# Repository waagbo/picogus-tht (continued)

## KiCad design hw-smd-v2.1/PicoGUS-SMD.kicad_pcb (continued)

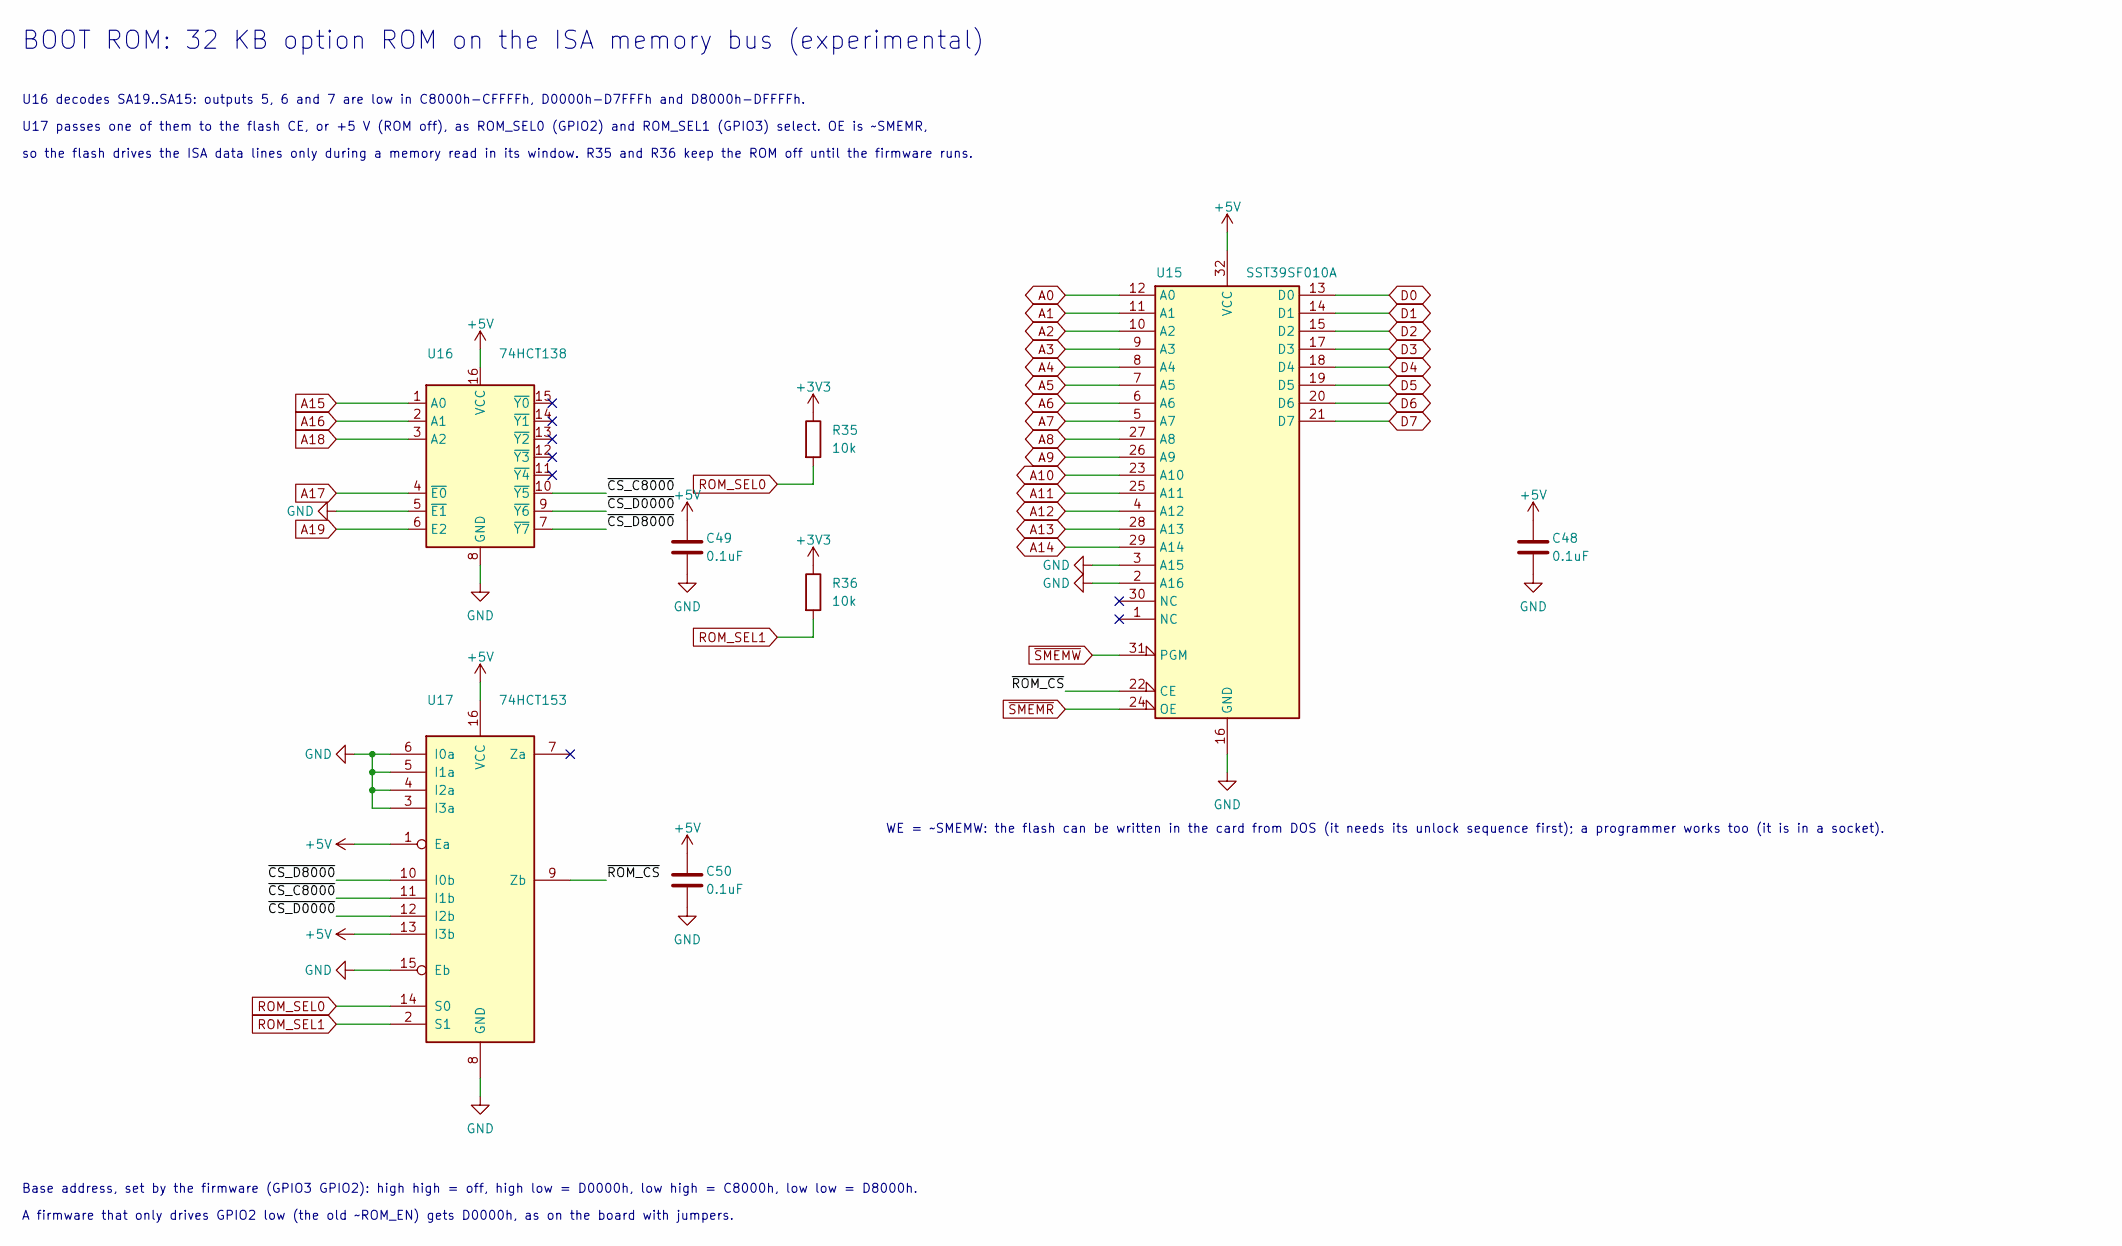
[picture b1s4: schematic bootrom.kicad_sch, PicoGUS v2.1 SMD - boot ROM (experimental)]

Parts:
C48, C49, C50: 0.1uF; C_0805_2012Metric_Pad1.18x1.45mm_HandSolder; MPN CL21B104KBCNNNC; DigiKey 1276-1003-1-ND
R35, R36: 10k; R_0805_2012Metric_Pad1.20x1.40mm_HandSolder; MPN RC0805FR-0710KL; DigiKey 311-10.0KCRCT-ND
U15: SST39SF010A; PLCC-32_THT-Socket; MPN SST39SF010A-70-4C-NHE; DigiKey SST39SF010A-70-4C-NHE-ND
U16: 74HCT138; SOIC-16_3.9x9.9mm_P1.27mm; MPN 74HCT138D,653; DigiKey 1727-2835-1-ND
U17: 74HCT153; SOIC-16_3.9x9.9mm_P1.27mm; MPN 74HCT153D,653; DigiKey 1727-74HCT153D,653CT-ND

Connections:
+3V3: R35.1, R36.1; also elsewhere on the board
+5V: C48.1, C49.1, C50.1, U15.32 (VCC), U16.16 (VCC), U17.1 (Ea), U17.13 (I3b), U17.16 (VCC); also elsewhere on the board
/Boot ROM/~CS_C8000: U16.10 (~Y5), U17.11 (I1b)
/Boot ROM/~CS_D0000: U16.9 (~Y6), U17.12 (I2b)
/Boot ROM/~CS_D8000: U16.7 (~Y7), U17.10 (I0b)
/Boot ROM/~ROM_CS: U15.22 (CE), U17.9 (Zb)
A0: U15.12 (A0); also elsewhere on the board
A1: U15.11 (A1); also elsewhere on the board
A2: U15.10 (A2); also elsewhere on the board
A3: U15.9 (A3); also elsewhere on the board
A4: U15.8 (A4); also elsewhere on the board
A5: U15.7 (A5); also elsewhere on the board
A6: U15.6 (A6); also elsewhere on the board
A7: U15.5 (A7); also elsewhere on the board
A8: U15.27 (A8); also elsewhere on the board
A9: U15.26 (A9); also elsewhere on the board
A10: U15.23 (A10); also elsewhere on the board
A11: U15.25 (A11); also elsewhere on the board
A12: U15.4 (A12); also elsewhere on the board
A13: U15.28 (A13); also elsewhere on the board
A14: U15.29 (A14); also elsewhere on the board
A15: U16.1 (A0); also elsewhere on the board
A16: U16.2 (A1); also elsewhere on the board
A17: U16.4 (~E0); also elsewhere on the board
A18: U16.3 (A2); also elsewhere on the board
A19: U16.6 (E2); also elsewhere on the board
D0: U15.13 (D0); also elsewhere on the board
D1: U15.14 (D1); also elsewhere on the board
D2: U15.15 (D2); also elsewhere on the board
D3: U15.17 (D3); also elsewhere on the board
D4: U15.18 (D4); also elsewhere on the board
D5: U15.19 (D5); also elsewhere on the board
D6: U15.20 (D6); also elsewhere on the board
D7: U15.21 (D7); also elsewhere on the board
GND: C48.2, C49.2, C50.2, U15.2 (A16), U15.3 (A15), U15.16 (GND), U16.5 (~E1), U16.8 (GND), U17.3 (I3a), U17.4 (I2a), U17.5 (I1a), U17.6 (I0a), U17.8 (GND), U17.15 (Eb); also elsewhere on the board
ROM_SEL0: R35.2, U17.14 (S0); also elsewhere on the board
ROM_SEL1: R36.2, U17.2 (S1); also elsewhere on the board
~SMEMR: U15.24 (OE); also elsewhere on the board
~SMEMW: U15.31 (PGM); also elsewhere on the board

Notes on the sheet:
BOOT ROM: 32 KB option ROM on the ISA memory bus (experimental)
U16 decodes SA19..SA15: outputs 5, 6 and 7 are low in C8000h-CFFFFh, D0000h-D7FFFh and D8000h-DFFFFh.
U17 passes one of them to the flash CE, or +5 V (ROM off), as ROM_SEL0 (GPIO2) and ROM_SEL1 (GPIO3) select. OE is ~SMEMR,
so the flash drives the ISA data lines only during a memory read in its window. R35 and R36 keep the ROM off until the firmware runs.
WE = ~SMEMW: the flash can be written in the card from DOS (it needs its unlock sequence first); a programmer works too (it is in a socket).
Base address, set by the firmware (GPIO3 GPIO2): high high = off, high low = D0000h, low high = C8000h, low low = D8000h.
A firmware that only drives GPIO2 low (the old ~ROM_EN) gets D0000h, as on the board with jumpers.

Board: 4 copper layers, 102 parts (0 on the bottom side), 144 nets, no tracks yet.

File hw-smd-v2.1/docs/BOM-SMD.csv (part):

References,Qty,Value,Package,Footprint,Description,Manufacturer,MPN,DigiKey PN,DigiKey link,LCSC PN,Part number,Notes
"U1, U2",2,SN74CB3T3257,TSSOP-16,TSSOP-16_4.4x5mm_P0.65mm_HandSolder_TestPads,"Quad 2:1 FET mux/demux, 5V-tolerant, TSSOP-16 (hand-solder footprint with a test pad per pin)",Texas Instruments,SN74CB3T3257PWR,296-17850-1-ND,https://www.digikey.no/no/products/result?keywords=296-17850-1-ND,C544573,as on THT v2.1 (docs/BOM-THT.csv),"Exists only as TSSOP (and smaller): 0.65 mm pitch, flux and drag soldering. The footprint has longer toes and a test pad per pin."
U3,1,74AHC14,SOIC-14,SOIC-14_3.9x8.7mm_P1.27mm,"Hex Schmitt inverter, 3V3, 5V-tolerant inputs, SOIC-14",Diodes Inc,74AHC14S14-13,31-74AHC14S14-13CT-ND,https://www.digikey.no/no/products/result?keywords=31-74AHC1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,,hw-smd BOM (2026-09-29),
"U4, U5",2,74AHC00,SOIC-14,SOIC-14_3.9x8.7mm_P1.27mm,"Quad NAND, 3V3, 5V-tolerant inputs, SOIC-14",Texas Instruments,SN74AHC00DR,296-4509-1-ND,https://www.digikey.no/no/products/result?keywords=296-4509-1-ND,,checked 2026-11-24,"DigiKey product page: active, SOIC-14 (3.9 mm body)."
U6,1,74AHCT126,SOIC-14,SOIC-14_3.9x8.7mm_P1.27mm,"Quad tri-state buffer on +5V, OE driven from 3V3, A tied low: open-drain drivers for MIDI and I/O CH RDY, SOIC-14",Texas Instruments,SN74AHCT126DR,296-4658-1-ND,https://www.digikey.no/no/products/result?keywords=296-4658-1-ND,,checked 2026-11-24,"DigiKey product page: active, SOIC-14 (3.9 mm body)."
U7,1,74AHC244,SOIC-20 wide,SOIC-20W_7.5x12.8mm_P1.27mm,"Octal buffer, 3V3, 5V-tolerant inputs, SOIC-20 wide (1.27 mm pitch)",Texas Instruments,SN74AHC244DWR,296-1096-1-ND,https://www.digikey.no/no/products/result?keywords=296-1096-1-ND,,checked 2026-11-24,"DigiKey product page: active, SOIC-20 wide (7.5 mm body)."
U9,1,MCP1826S-3302E/DB,SOT-223,SOT-223-3_TabPin2,"3.3V 1A LDO, SOT-223 (VIN 1, GND 2/tab, VOUT 3), 250 mV dropout",Microchip,MCP1826ST-3302E/DB,MCP1826ST-3302E/DBCT-ND,https://www.digikey.no/no/products/result?keywords=MCP1826ST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,,checked 2026-11-24,"Microchip datasheet DS22057B: SOT-223-3, pin 1 VIN, pin 2 and tab GND, pin 3 VOUT; output capacitor 1 uF minimum, 22 uF maximum recommended. This is the tape version of MCP1826S-3302E/DB (DigiKey sells that one in tubes only: MCP1826S-3302E/DB-ND)."
U10,1,PCM5100A,TSSOP-20,TSSOP-20_4.4x6.5mm_P0.65mm_HandSolder,"I2S DAC, TSSOP-20 on hand-solder toes without test pads, so that its capacitors sit at the pins",Texas Instruments,PCM5100APWR,296-36705-1-ND,https://www.digikey.no/no/products/result?keywords=296-36705-1-ND,C131154,as on THT v2.1 (docs/BOM-THT.csv),"Exists only as TSSOP-20. On hand-solder toes without test pads here, so that its capacitors sit at the pins."
U11,1,NE5532,SOIC-8,SOIC-8_3.9x4.9mm_P1.27mm,"Dual low-noise audio op-amp, SOIC-8: line-out summing mixer on ISA +/-12V",Texas Instruments,NE5532DR,296-13622-1-ND,https://www.digikey.no/no/products/result?keywords=296-13622-1-ND,,hw-smd BOM (2026-09-29),
U12,1,Core2350B,Waveshare Core2350B2 module on four 2x8 2.54 mm sockets,Waveshare_Core2350B,"Waveshare Core2350B RP2350B module: Core2350B2 (8 MB PSRAM) recommended, B0/B1 also work",Waveshare,Core2350B2,"not stocked: waveshare.com SKU 31690 (B2), 31689 (B0), 31818 (B1)",,not at LCSC: waveshare.com,as on THT v2.1 (docs/BOM-THT.csv),"The RP2350B (QFN-80), flash, crystal and 8 MB PSRAM have no THT form; the module carries them."
U13,1,M62429L,SOIC-8,SOIC-8_3.9x4.9mm_P1.27mm,"2-channel digital volume control (Waveblaster volume, GPIO24/25), SOIC-8; powered from AVDD (3.3V) as on v2.0, so use a 3-5.5V part (Wuxi I-core M62429L)",Wuxi I-core,M62429L.TR,"not stocked: LCSC only (DigiKey marketplace 2156-M62429FP#CF0J-ND is the 4.5-5.5V Renesas part, MOQ 143)",,C52260216,as on THT v2.1 (docs/BOM-THT.csv),"Wuxi I-core M62429L, at LCSC only. Any M62429 that runs from 3.3 V fits (v2.0 used LCSC C668666)."
U14,1,RM2,Raspberry Pi Radio Module 2: 21 castellated pads at 1.5 mm pitch,RaspberryPi_RM2_HandSolder,"Raspberry Pi Radio Module 2 (RMC20452T): CYW43439 WiFi 4 + Bluetooth 5.2, gSPI host interface, 14.5 x 16.5 mm castellated module (hand-solder footprint)",Raspberry Pi,RMC20452T,Farnell 4737257 (DigiKey not looked up),,buy at Farnell: 4737257 (LCSC not looked up),as on THT v2.1 (docs/BOM-THT.csv),"Optional: without U14 (and R33, R34, C47) the card works as before. Sits at the bracket end with its antenna at the card edge; needs a plastic bracket (or none) to radiate, see the README."
U15,1,SST39SF010A,PLCC-32 flash,PLCC-32_THT-Socket,"Boot ROM: 128 KB 5 V flash in a through-hole PLCC-32 socket; the first 32 KB appear at the base address (A15/A16 low); CE from the decoder, OE = ~SMEMR; read only in the card (WE high)",Microchip,SST39SF010A-70-4C-NHE,SST39SF010A-70-4C-NHE-ND,https://www.digikey.no/no/products/result?keywords=SST39SF01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,not at LCSC: C645930 (SST39SF010A-70-4C-NHE) 0 in stock on 2026-11-12; buy at DigiKey,as on THT v2.1 (docs/BOM-THT.csv),"EXPERIMENTAL boot ROM (U15, U16, U17, C48, C49, C50, R35, R36 and the socket): leave all of it out and the card is the plain v2.1."
U16,1,74HCT138,SOIC-16,SOIC-16_3.9x9.9mm_P1.27mm,"Boot ROM address decoder, SOIC-16: one output per 32 KB block of C0000h-DFFFFh (SA19 high, SA17 low, SA18 SA16 SA15 select), always enabled; U17 passes one output on to the flash",Nexperia,"74HCT138D,653",1727-2835-1-ND,https://www.digikey.no/no/products/result?keywords=1727-2835-1-ND,,checked 2026-11-24,"DigiKey product page: active, SO16 (3.9 mm body)."
U17,1,74HCT153,SOIC-16,SOIC-16_3.9x9.9mm_P1.27mm,"Boot ROM base address, SOIC-16 (half b; half a unused): passes U16 output 6 (D0000h), 5 (C8000h) or 7 (D8000h), or +5 V (ROM off), to the flash CE for ROM_SEL1/ROM_SEL0 = 10, 01, 00 or 11. TTL inputs for the 3.3 V GPIOs",Nexperia,"74HCT153D,653","1727-74HCT153D,653CT-ND","https://www.digikey.no/no/products/result?keywords=1727-74HCT153D,653CT-ND",,checked 2026-11-24,"DigiKey product page: active, SO16 (3.9 mm body)."
"J2, J4",1,1x40 breakaway header,through-hole PinHeader,PinHeader_1x03_P2.54mm_Vertical,"1x3 header: SWCLK, GND, SWDIO",Sullins,PREC040SAAN-RC,S1012EC-40-ND,https://www.digikey.no/no/products/result?keywords=S1012EC-40-ND,C2337 (BOOMELE 2.54-1*40P),as on THT v2.1 (docs/BOM-THT.csv),
J3,1,IRQ/DMA,through-hole PinHeader,PinHeader_2x09_P2.54mm_Vertical,2x9 header + 3 jumpers,Amphenol,10129381-918001BLF,609-10129381-918001BLF-ND,https://www.digikey.no/no/products/result?keywords=609-10129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,C492426 (XFCN PZ254V-12-18P),as on THT v2.1 (docs/BOM-THT.csv),
J5,1,USB-A host,through-hole USB-A,USB_A_Molex_67643_Horizontal_ShieldPin5,"USB-A receptacle, through hole (joystick/mouse/storage host port); THT v1.3.2 part and position, for its bracket",Molex,0676430910,WM4993-ND,https://www.digikey.no/no/products/result?keywords=WM4993-ND,C2798029,as on THT v2.1 (docs/BOM-THT.csv),At the THT v1.3.2 position (x 208.64) for the v1.3.2 bracket's USB-A cut-out.
J6,1,USB-C program,USB-C receptacle,USB_C_Receptacle_GCT_USB4085,"USB-C receptacle, USB 2.0, through hole (programming / BOOTSEL; shares D+/D- with J5)",GCT,USB4085-GF-A,2073-USB4085-GF-ACT-ND,https://www.digikey.no/no/products/result?keywords=2073-USB4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,C7095263,as on THT v2.1 (docs/BOM-THT.csv),"The only all-through-hole USB-C 2.0 receptacle: 0.85 mm pin pitch, the finest joint on the card."
J7,1,SJ1-3535NG,through-hole Jack,Jack_3.5mm_CUI_SJ1-3535NG_Horizontal,"3.5mm jack, black (MIDI out)",Same Sky (CUI),SJ1-3535NG,CP1-3535NG-ND,https://www.digikey.no/no/products/result?keywords=CP1-3535NG-ND,C2884945 (XKB PJ-325C5-B),as on THT v2.1 (docs/BOM-THT.csv),
J8,1,Waveblaster,through-hole Wavetable,Wavetable_NoMountingHoles,2x13 male header for a Waveblaster daughterboard,Sullins,PEC13DAAN,35-PEC13DAAN-ND,https://www.digikey.no/no/products/result?keywords=35-PEC13DAAN-ND,C2894974 (HCTL PZ254-2-13-Z-8.5),as on THT v2.1 (docs/BOM-THT.csv),
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
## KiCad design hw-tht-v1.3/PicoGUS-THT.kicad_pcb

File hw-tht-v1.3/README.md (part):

# PicoGUS THT (through-hole) v1.3.2 – based on PicoGUS v1.2

Board revision **v1.3.2**: the v1.3.1 (rev B) THT board on a 102 mm outline, with
the fine-pitch chips soldered straight to the card and a test pad on every one of their pins.

* **U3/U4** (SN74CB3T3257, TSSOP-16) and **U9** (PCM5100A, TSSOP-20; the PCM5101A/5102A fit too) only exist as TSSOPs. They are soldered to
  the card on hand-solder footprints, and **every pin has its own 0.7 mm round test pad** in line with it, for a
  probe, a meter or a scope (see [U3/U4 and U9 with a test pad per pin](#u3u4-and-u9-with-a-test-pad-per-pin)).
  The TSSOP-to-DIP adapter boards of the earlier v1.3.2 layout are gone, and so are their sockets.
* **The GY-PCM5102 module option (J10) is gone.** The on-board DAC is always fitted.
* **New placement** of the DAC block, the mixer and the jacks (2026-10-31 / 2026-11-01): the DAC sits above U3/U4
  with its analog side facing east toward the output filter and the mixer above it, MIDI OUT at the top of the
  bracket end and LINE OUT below WT VOL (see [Placement](#placement)).
* **C36** (U9 charge-pump decoupling) is a through-hole 0.1 µF disc, and all eight DAC decoupling discs sit on the
  side of U9 where their pins are (see [DAC decoupling](#dac-decoupling)).
* **C8/C10** (U8 PSRAM decoupling) are the v1.3.1 through-hole discs, next to U8.
* **1.84 mm shorter**: 102.0 mm long over the outline (v1.3.1: 103.8 mm), trimmed at the bracket end. The bracket tab
  holes H1/H2 are 1.70 mm further from the bracket plate, so the card needs a bracket with longer tabs (see
  [Bracket](#bracket)).
* **No artwork on the back silkscreen**: the princess artwork is to be UV printed instead. The back texts stay.

The main board is through-hole apart from **U3, U4, U9** (TSSOP, 0.65 mm pitch), **U8** (APS6404L PSRAM, SOIC-8,
1.27 mm pitch) and the optional **U12** (USBLC6-2SC6, SOT-23-6), all on the front. The rest of the circuit is
v1.3.1's: USB-A host port, Waveblaster header, op-amp mixer.

> **Status: v1.3.2, ready to order (tag `v1.3.2-tht`); not built or tested yet.** The placement of 2026-11-01 is
> routed on two layers (2026-11-01).
> The schematic's ERC is the same as v1.3.1's (280 warnings, 0 errors). DRC with schematic parity finds 0
> unconnected items and, as errors, only the 12 accepted courtyard overlaps in the logic column, so
> `hw-common/tools/jlcpcb.sh` exports with `ALLOW_DRC=courtyards_overlap`; `build/jlcpcb/` holds that export (not in git: the repository
> ignores `build/`). The first routed TSSOP layout (commit 298e993) was reviewed independently; this placement
> shortens the DAC outputs and the mixer's summing nodes that review pointed at, and its route applies the review's
> rules from the start. Compared with the routed DIP-adapter layout (commit d5c4a85) it is better on I2S, the
> DAC-to-mixer path and the vias at silkscreen text, and worse on the ISA data-bus length, which the test pads set:
> see [Layout status](#layout-status).

Files:

| File | What |
|---|---|
| `PicoGUS-THT.kicad_pro/.kicad_sch/.kicad_pcb` | KiCad **10** project (the root sheet is the v1.2 logic). The board is routed |
| `audio.kicad_sch` | PCM510x DAC sheet: U9 a TSSOP-20 with test pads, C36 a THT disc, no J10 |
| `wavetable.kicad_sch` | Waveblaster header, WT volume, op-amp mixer, line-out jack (as v1.3.1) |
| `usb.kicad_sch` | USB host port (J11 USB-A, F1, C34/C35, U12) (as v1.3.1) |
| `PicoGUS-THT-schematic.pdf` | Schematic PDF |
| `docs/BOM-THT.csv` | BOM with DigiKey **and** LCSC part numbers, stock (2026-11-07) and a digikey.no link per line |
| `docs/BOM-THT-digikey.csv`, `-lcsc.csv`, `-mouser.csv` | DigiKey, LCSC and Mouser upload files for one board, made from `BOM-THT.csv` (see [Ordering](#ordering)); the optional parts (sockets, U12) are at the bottom, marked "(optional)" |
| `docs/renders/` | 3D renders of the routed card: red from the front and the back, green, purple, white and black from the front (ENIG; white silkscreen, black on white). Made with `hw-common/tools/render.sh` |
| `docs/figures/` | Figures for the README's exceptions and design choices (e.g. the test pads, the placement options, the accepted courtyard overlaps), with the scripts that make them in `docs/figures/src/` |

The shared `PiGUS library` symbols and footprints are linked from `hw-common/`, like the other boards. **New in the
shared library for v1.3.2:** `TSSOP-16_4.4x5mm_P0.65mm_HandSolder_TestPads` (U3, U4),
`TSSOP-20_4.4x6.5mm_P0.65mm_HandSolder_TestPads` (U9) and `RPi_Pico_SMD_TH_USB_NoSWD` (U1, see
[102 mm board](#102-mm-board)), in `hw-common/PiGUS library.pretty`; DRC's library check finds the board's U1, U3,
U4 and U9 identical to them. The adapter footprints and adapter 3D models of the earlier v1.3.2 layout are removed;
the older `DIP-16_W7.62mm_TSSOP-16_Nested` stays unused.

Every part has a 3D model. The ones KiCad 10's library does not have are in `hw-common/parts`, reached through the
project folder's `parts` link: the CUI SJ1-3535NG jacks (J8 green; J5 a black copy of the same CUI model), the Alps
RK09712 pot (RV1) and a simple generated Bourns MF-R050 (F1). U3/U4/U9 use KiCad's TSSOP models, U1 KiCad's own
`RaspberryPi_Pico.step`, and J9's header model path is fixed. The library footprints carry the same models as the
board.

## What changed compared to v1.3.1

### U3/U4 and U9 with a test pad per pin

| | U3, U4 (SN74CB3T3257, TSSOP-16) | U9 (PCM5100A, TSSOP-20) |
|---|---|---|
| Footprint | `PiGUS library:TSSOP-16_4.4x5mm_P0.65mm_HandSolder_TestPads` | `PiGUS library:TSSOP-20_4.4x6.5mm_P0.65mm_HandSolder_TestPads` |
| Courtyard | 11.4 × 5.75 mm | 11.4 × 7.05 mm |
| Position (centre) | U3 (150.22, 110.10), U4 (161.44, 110.12), both 90° (pin 1 at the bottom left) | (156.10, 84.53), 180° (pin 1 at the bottom right) |

* **Land pattern**: the TSSOP hand-solder pads (1.775 × 0.40 mm at ±3.01 mm from the centre, toes out to ±3.9 mm),
  long enough to put an iron on each pin.
* **One test pad per pin**: a 0.7 mm round pad (bare copper, `testpoint` property) straight out from each pin,
  joined to it by a 0.2 mm track. The pads alternate between two columns, 4.45 and 5.10 mm from the centre, so each
  sits on its own pin's line and 1.3 mm from the next pad in its column; the track to an outer pad passes between two
  inner pads with 0.2 mm on each side, the board's normal clearance. The footprint has the pin numbers at the column
  ends in 0.8 mm silk. The pads make every pin reachable for a probe, a meter or a scope clip, and a solder bridge
  between two pins shows up as a short between their pads.
* **Routing**: an outer-column pin is routed from its test pad. An inner-column pin that is used gets a 0.2 mm
  escape stub straight on from its test pad, centred between the two outer pads, to 5.80 mm from the centre, and is
  routed from the stub end (26 stubs; the two left unused are removed after routing, see
  [Layout status](#layout-status)). The router cannot squeeze a track between two outer pads (0.6 mm
  gap) any other way, and the stubs keep the 0.2 mm clearance exactly as the pin-to-pad tracks do.
* **Pin numbers stay the schematic's**: U9 is 1 CPVDD, 2 CAPP, 3 CPGND, 4 CAPM, 5 VNEG, 6 OUTL, 7 OUTR, 8 AVDD,
  9 AGND, 10 DEMP, 11 FLT, 12 SCK, 13 BCK, 14 DIN, 15 LRCK, 16 FMT, 17 XSMT, 18 LDOO, 19 DGND, 20 DVDD.
* The symbols' `Adapter` fields and the adapter wording in the descriptions and sheet notes are gone; the root sheet
  says "SMD: U3/U4 TSSOP-16, U9 TSSOP-20 (with test pads), U8 SOIC-8, U12 opt.".

![Test pads on U9 (and U3/U4): the TSSOP-20 land pattern to scale with its 20 test pads in two staggered columns
(inner 4.45 mm, outer 5.10 mm from the centre, 1.3 mm between two pads of a column), the 0.2 mm track from each pin
to its pad passing between two pads with 0.2 mm clearance on each side, and the escape stubs that carry an
inner-column pin out between two outer pads to the routing](docs/figures/test-pads.png)

### No GY-PCM5102 module option

J10 (the GY-PCM5102 module, soldered on male pins over the DAC area as the alternative to the on-board DAC since
v1.3.0) is gone from the schematic and the board. Its dashed silkscreen outline and the "DAC -OR- GY-PCM5102"
heading went with it; the heading now just says "DAC". Its nets (BCK, DIN, LRCK, +5V, GND, AUDIO_L/R) stay,
because U9's circuit uses them. U9, C12–C20, C36, FB3, R7 and R8 are always fitted. The BOM's J10 line and its
"DAC AREA: leave out ..." notes are gone.

### DAC decoupling

C36 (U9 CPVDD decoupling) is the board's standard 0.1 µF 50 V X7R radial disc (Murata RDER71H104K0M1H03A, the 0.1 µF
line of the BOM) instead of v1.3.1's 0603. U9 stands at 180° with its analog pins 1–10 facing east, toward the output
filter and the mixer, and its digital pins 11–20 facing west. Each disc sits on the side of the pins it serves:

* **East, beside pins 1–10**, in rows 3.0 mm apart: C15 (AVDD, 10 µF) and C13 (AVDD) at the top, the output
  resistors R8/R7 level with pins 7/6, then C16 (CAPP/CAPM) and C17 (VNEG); the filter discs C20/C19 end the C13 and
  C16 rows on the east.
* **South, under pins 1–3**: C36 (CPVDD/CPGND), with C14 (+3V3) below it.
* **West, beside pins 11–20**: C18 (LDOO) level with pins 17–19 and C12 (DVDD) below pin 20. FB3 (the AVDD bead)
  runs along the top of the block from the +3V3 side in the west to its AVDD pad above C15.

Distances from the chip pin to the nearest pad of the part, straight line:

| Part | Pins | DIP-adapter layout (d5c4a85) | First routed TSSOP layout (298e993) | Now |
|---|---|---|---|---|
| C36 | CPVDD (1) / CPGND (3) | 2.7 / 9.2 mm | 9.7 / 5.6 mm | 3.6 / 5.4 mm |
| C16 | CAPP (2) / CAPM (4) | 3.2 / 3.2 mm | 9.5 / 4.6 mm | 9.7 / 5.5 mm |
| C17 | VNEG (5) | 6.6 mm | 9.6 mm | 8.1 mm |
| C13 | AVDD (8) / AGND (9) | 4.7 / 6.7 mm | 5.1 / 9.6 mm | 5.6 / 9.9 mm |
| C15 | AVDD (8) | 7.3 mm | 12.4 mm | 7.8 mm |
| C18 | LDOO (18) / DGND (19) | 3.5 / 9.1 mm | 4.5 / 9.5 mm | 4.0 / 9.0 mm |
| C12 | DVDD (20) / DGND (19) | 4.5 / 8.4 mm | 2.6 / 6.4 mm | 5.4 / 3.8 mm |
| R7 / R8 | OUTL (6) / OUTR (7) | 3.0 / 2.8 mm | 6.8 / 8.2 mm | 4.7 / 4.6 mm |
| FB3 | AVDD (8) | 2.8 mm | 14.1 mm | 6.3 mm |

* **C36 is the nearest disc to its pin** (3.6 mm from CPVDD), as the PCM510x datasheet asks for the charge-pump
  supply. C16 (the flying capacitor between CAPP and CAPM) stays 9.7 mm from CAPP: it shares the east column with
  the output resistors, which sit level with their pins.
* C16 and C17 were 0.02 mm off the 3.0 mm row grid in the uploaded placement (y 88.60 / 91.60), so C16's courtyard
  touched R7's by 0.015 mm; they are now at y 88.62 / 91.62, in line with C19.
### C8/C10: through-hole discs next to U8

| Ref | Part | DigiKey | LCSC |
|---|---|---|---|
| C8 | 0.1 µF 50 V X7R radial disc, 5.0 mm pitch, Murata RDER71H104K0M1H03A (the BOM's 0.1 µF line) | 490-9144-1-ND | C527620 |
| C10 | 1 µF 50 V X7R radial disc, 5.0 mm pitch, Murata RDER71H105K2M1H03A | 490-9146-1-ND | C1620132 |

These are the v1.3.1 parts again (the routed layout of commit 8dbb6c6 had 0805s on the back under U8). U8 (SOIC-8,
front) stands at 90° at (190.00, 92.47): pins 1–4 along the bottom (y 94.95, pin 1 at the left), pins 5–8 along the
top (y 90.00), pin 8 (+3V3) at (188.09, 90.00), pins 3/4/7 GND. C8 (0.1 µF) stands vertically left of U8, its +3V3
pad 2.50 mm straight left of pin 8 at (185.59, 90.00) and its GND pad at (185.59, 95.00); C10 (1 µF) lies above U8,
+3V3 pad at (187.09, 87.00), GND pad at (192.09, 87.00). With them, every SMD part (U3, U4, U8, U9, U12) is on the
front.

### 102 mm board

The bracket end of the outline is trimmed 1.84 mm (x 220.13 → 218.29). The board is 101.90 × 99.85 mm at the
outline's line centres, 102.00 × 99.95 mm over its 0.1 mm lines (v1.3.1 and the routed v1.3.2 layout: 103.74 ×
99.85 / 103.84 × 99.95 mm). JLCPCB quoted USD 24.50 for 10 black ENIG 2-layer boards at 102.0 mm (and 101.9 mm), USD 33 at
102.7 mm and 33.53 at 103.74 mm (2026-10-28). The ISA fingers, the other three edges and the bracket plate's place in the case do not change.
To keep copper at least 0.35 mm from the new edge, these parts moved left, away from the bracket:

| Part | Moved | Now | Nearest copper to the new edge |
|---|---|---|---|
| H1 / H2 (bracket tab holes) | 1.70 mm | x 214.70 | 0.39 mm (their 6.4 mm pads) |
| J5 (MIDI out) | 1.10 mm | x 217.00 | 0.39 mm (sleeve pad) |
| J8 (line out) | 0.90 mm | x 217.00 | 0.39 mm (sleeve pad) |
| U1 (Pico), with its five test-pad rule areas and its two micro-USB relief slots | 1.35 mm | centre x 192.88, pin 1 (217.01, 100.00) | 0.36 mm (TP2/TP3); the slots (centre x 216.88) end 0.41 mm from the edge |
| U4 / U3 | – | TSSOP centres x 161.44 / 150.22 (re-placed for the soldered TSSOPs, see [Placement](#placement)) | – |

J11 and RV1 stay where they were. The distances are to the outline's line centre. Between these parts and the edge
there is no room for a track or a via: 0.3 mm copper-to-edge, a 0.2 mm track and 0.2 mm clearance need 0.7 mm. What
the trim means for the bracket is under [Bracket](#bracket): the tab holes need a bracket with 1.70 mm longer tabs.

![The bracket end trimmed from 103.74 to 101.90 mm: old (dashed) and new outline with the trimmed 1.84 mm strip, the
bracket plate and tabs from User.Drawings, the tab holes H1/H2 1.70 mm further in (7.03 mm from the plate instead of
5.33), J5, RV1, J8, J11 and the Pico's USB end with their moves and nearest copper to the new edge, and a table of the
x positions](docs/figures/bracket-trim.png)

* **U1 uses the new footprint `PiGUS library:RPi_Pico_SMD_TH_USB_NoSWD`**: `RPi_Pico_SMD_TH_USB` without the
  three SMD castellation pads at the SWD end (pads 41–43: SWCLK and SWDIO, both not connected, and GND; their
  through-holes stay) and with the courtyard 0.2 mm past the module there instead of 0.5 mm. With the old
  courtyard, U4's would overlap the Pico's by 0.25 mm.
* The Pico's USB end (x 218.38) is now flush with the edge: 0.09 mm past the outline's line centre (0.40 mm inside
  it before).
* The Pico's far end is at x 167.38, 2.9 mm under a full-size Waveblaster daughterboard's outline (x 170.32; routed
  v1.3.2 layout 1.6 mm, v1.3.1 1.3 mm). That matters for a socketed Pico (see [Socket build](#socket-build)).

### Placement

The board holds a hand arrangement on the 102 mm outline: the logic column and the Pico from 2026-10-28, the jack
arrangement for the soldered TSSOPs from 2026-10-31, and the DAC block and mixer as rearranged on 2026-11-01 after a
first route, routed afterwards (see [Layout status](#layout-status)).

* **Logic column at the left edge** (as on the earlier v1.3.2 layout). U10, U7, U6 and U5 (DIP-14, 90°, pin 1 at the
  left as on v1.3.1) are stacked in line with U2 at x 120.07, 12.05 mm apart (pin 1 at y 65.62 / 77.67 / 89.71 /
  101.76; U2: 113.81). Each chip's decoupling cap lies horizontally (0°) in the gap above it, pad 1 2.21 mm straight
  above the supply pin (pin 14; U2: pin 20): C21 (U10, +5V), C6 (U7), C9 (U6), C7 (U5) and C4 (U2), pads at x
  120.07 / 125.07, y 55.79 / 67.83 / 79.88 / 91.93 / 103.97. R18, R5, R6 and R17 stand vertically (−90°) in one
  column at x 138.60, at the chips' right-hand ends (pad 1 at y 56.73 / 68.78 / 80.82 / 92.87). The column is
  packed tighter than the courtyards allow: 12 overlaps, accepted (see [Layout status](#layout-status)). The five
  references stand vertically at the board edge (x 117.50), centred on each chip.
* **U2** (DIP-20, 90°) at the lower left, pin 1 (120.07, 113.81). **J1** (the IRQ/DMA jumper block) at pin 1
  (136.03, 124.91), 90°, with its `IRQ`/`DMA` labels and numbers above it.
* **U3/U4** (TSSOP-16 with test pads, 90°): U3 (D0–D3, A0–A3) at (150.22, 110.10) and U4 (D4–D7, A4–A7) at
  (161.44, 110.12), pin 1 at the bottom left. Their decoupling discs C3/C5 lie above them at y 102.29 (C3's +3V3 pad
  at x 147.88, 4.8 mm from U3's pin 16), R2 at (160.97, 99.01).
* **DAC block, above U3/U4 and the Pico's far end**: U9 (TSSOP-20 with test pads) at (156.10, 84.53), 180°: pins
  11–20 (I2S, LDOO, DGND, DVDD) on its west side, pins 1–10 (charge pump, VNEG, outputs, AVDD, AGND) on its east side,
  facing the output filter and the mixer. East of it, in rows 3.0 mm apart (see [DAC decoupling](#dac-decoupling)):
  C15 (163.60, 76.53), C13 (168.60, 79.53), R8 (163.60, 82.60), R7 (163.62, 85.62), C16 (168.60, 88.62) and C17
  (163.60, 91.62), with the filter discs C20 (170.70, 79.53) and C19 (170.70, 88.62) at the east end. C36 (161.00,
  90.50) and C14 (156.00, 93.50) lie under U9's pins 1–3, C18 (149.10, 86.03) and C12 (153.60, 90.53) on its west
  side, and FB3 (the AVDD bead) along the top at (148.60, 77.03). `DAC` stands at (146.11, 92.10).
* **Mixer, above the DAC block**: U11 (DIP-8, 0°) at (173.00, 61.00), its feedback discs C30/C31 standing (90°) at
  its two ends, (170.12, 65.08) and (183.50, 67.00); C28 (+12VA) above it at (180.62, 54.08) and C29 (−12VA) below at
  (175.62, 75.08); R23/R24 (±12V 10 Ω) at (170.42, 57.50) / (170.42, 72.00); C32/C33 (47 µF) standing at x 184.62
  (y 57.12 / 70.08). The mixer resistors stay in two columns: R13, R11, R22, R10, R21 at x 189.43 (y 54.50 / 58.00 /
  65.00 / 72.50 / 79.50) and R20, R12, R19 at x 199.58 (y 61.50 / 69.00 / 76.00). `MIXER` at (171.12, 55.04).
* **C22/C23** (the 10 µF bipolar Waveblaster coupling caps) stand at the top next to J9, (174.00, 40.00) and
  (181.50, 40.00), −90°, with their references above them at y 38.00. C22's can is 0.48 mm outside a full-size
  daughterboard's outline (x 170.32) at nominal size.
* **Bracket end, top to bottom: MIDI OUT, WT VOL, LINE OUT.** J5 (MIDI out) at (217.00, 49.00) with its parts
  R3 (176.64, 46.50), R4 (186.80, 50.50), FB1 (189.50, 46.50) and FB2 (189.50, 50.50) along the top; RV1 (WT VOL)
  at (214.00, 61.40); J8 (line out) at (217.00, 75.50). The labels
  `MIDI OUT`, `WT VOL` and `LINE OUT` are left-aligned at x 204.0 (y 43.5 / 65.0 / 70.0).
* **USB host corner**: U8 (SOIC-8) at (190.00, 92.47), 90°, with C8/C10 next to it (see
  [C8/C10](#c8c10-through-hole-discs-next-to-u8)); U12 at (197.14, 91.45), F1 vertical at (204.00, 90.00), C35 at
  (200.00, 95.00), C34 at (202.30, 83.50).
* **Waveblaster side**: R16 at (150.00, 46.00), 0°; C24, C25 and C26 in a row at y 45.50 (x 146.90 / 143.00 /
  139.00).
* **Pico (U1)** at (192.88, 108.89), pin 1 (217.01, 100.00), and the bracket end (H1/H2, J11) as on the earlier
  v1.3.2 layout (see [102 mm board](#102-mm-board)).

**Why this arrangement.** Four placements of the DAC, mixer and jacks were compared before the first route, each
with the DAC discs on their pins and the logic-column labels as above: A (the first hand placement, DAC block high in
the middle), A2 (A with a DAC block turned 90°), C (that block in the middle with the mixer beside it) and D. In A2
and C, U9's I2S pins face away from the Pico, and a trial route of the three I2S nets alone (with the DAC outputs kept
clear) needed 232 and 238 mm; in A 171 mm; in D 122 mm. D had the shortest DAC-to-mixer path and the shortest
ratsnest overall and was routed first (commit 298e993). That route left the mixer's summing nodes 51 / 53 mm long
and the DAC outputs 19 / 20 mm, because the output filter sat above U9 and the mixer inputs far from U11. The
present arrangement keeps D's jacks and moves the DAC block 12.9 mm west with the output filter east of U9, between
it and the mixer, and turns U11 so that its feedback discs sit on its pins. Against D, in ratsnest length: summing
nodes 95.7 → 61.9 mm, DAC outputs 18.5 → 9.5 mm, mixer outputs 64.3 → 41.5 mm, AVDD and LDOO 26.5 → 15.6 mm; I2S
113.6 → 123.5 mm and the Waveblaster path behind C22/C23 56.0 → 75.4 mm are longer; all nets but GND 4229 → 4169 mm.

![The comparison before the first route (D became commit 298e993; the present arrangement grew out of it). Placements A, A2, C and D side by side: board outlines with the DAC area and the mixer area shaded, the I2S
ratsnest, the audio-path ratsnest and the digital ratsnest that crosses the DAC area, and a table of the trial I2S
route, I2S ratsnest, distances from the DAC area to the Pico and U8, digital ratsnest through the DAC and mixer areas,
DAC-to-mixer and Waveblaster paths, mixer summing nodes, line out, ±12V, SPI and total ratsnest](docs/figures/placement-options.png)

| Part | Routed DIP-adapter layout (d5c4a85) | Now |
|---|---|---|
| U3 / U4 | DIP-16 adapter pin 1 (146.53, 106.42) / (157.74, 106.44), 0° | TSSOP-16 centre (150.22, 110.10) / (161.44, 110.12), 90° |
| U9 | DIP-20 adapter pin 1 (146.00, 78.30), 90° | TSSOP-20 centre (156.10, 84.53), 180° |
| U11 | (173.02, 51.10), 90° | (173.00, 61.00), 0° |
| J5 (MIDI) / J8 (line out) | (217.00, 75.50) / (217.00, 49.10) | (217.00, 49.00) / (217.00, 75.50) |
| U8 | (189.00, 93.90), 0° | (190.00, 92.47), 90° |
| C8 / C10 | (191.50, 88.40) / (184.00, 88.40), 180° | (185.59, 90.00), −90° / (187.09, 87.00), 0° |
| J1 | (120.00, 123.70) | (136.03, 124.91) |
| FB3 | (164.10, 93.73), 90° | (148.60, 77.03), 0° |
| C3 / C5 | (153.50, 103.28) / (164.69, 103.34), 180° | (147.88, 102.29) / (158.88, 102.29), 0° |

Positions are footprint origins (pin 1 for the DIPs, the centre for the TSSOPs), in mm. 51 of the 88 footprints moved
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
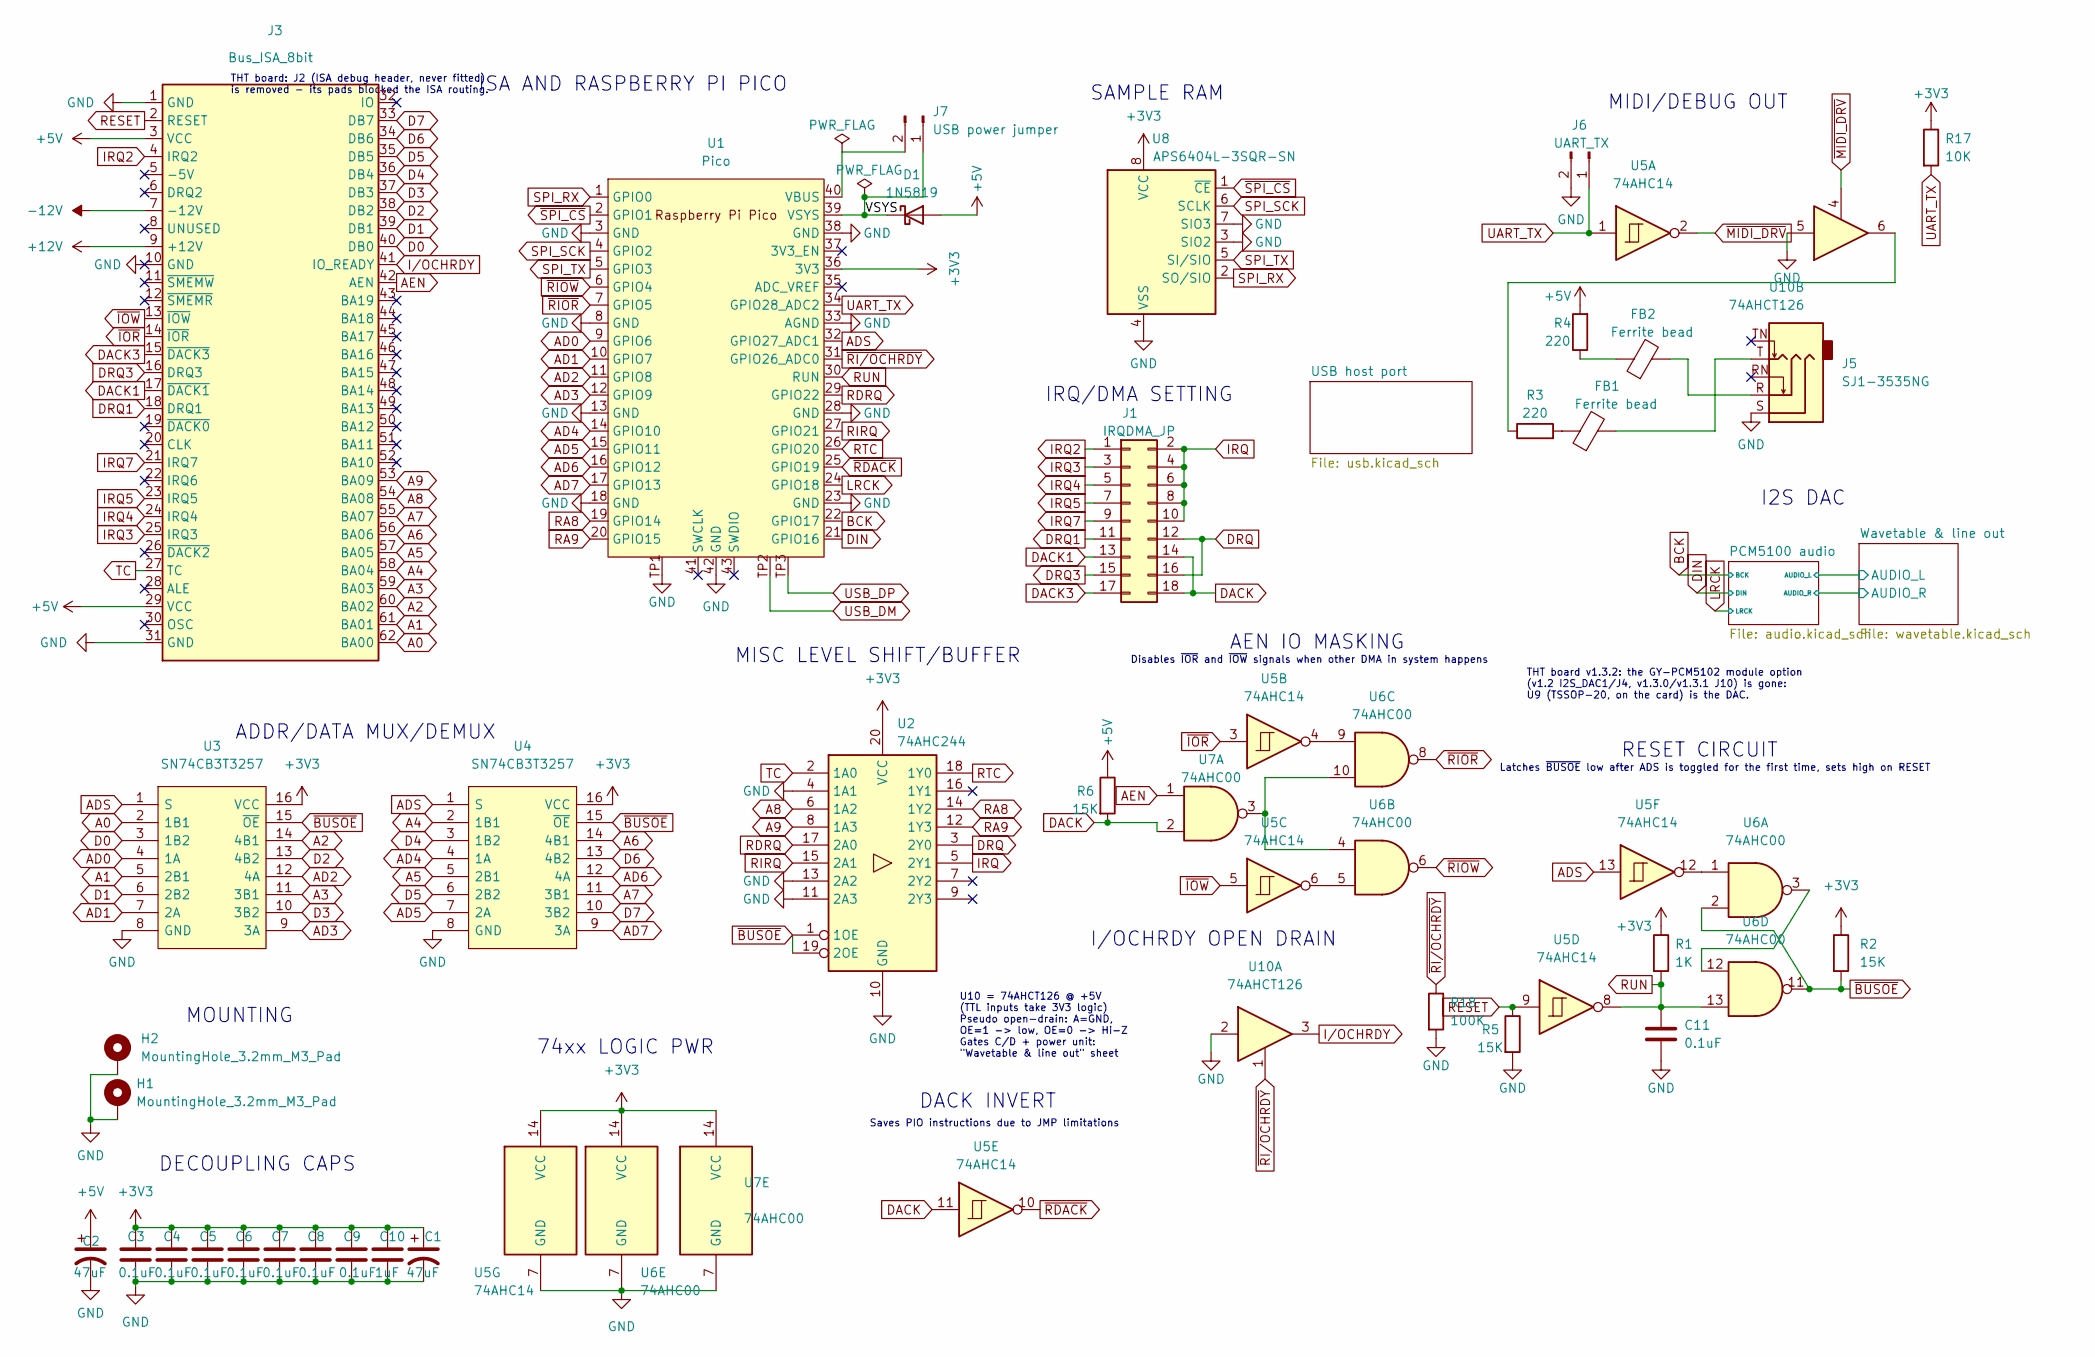
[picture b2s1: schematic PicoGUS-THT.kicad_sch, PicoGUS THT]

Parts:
C1, C2: 47uF; CP_Radial_D5.0mm_P2.00mm; MPN 35YXJ47M5X11; DigiKey 1189-2919-ND
C3, C4, C5, C6, C7, C8, C9, C11: 0.1uF; C_Disc_D5.0mm_W2.5mm_P5.00mm; MPN RDER71H104K0M1H03A; DigiKey 490-9144-1-ND
C10: 1uF; C_Disc_D5.0mm_W2.5mm_P5.00mm; MPN RDER71H105K2M1H03A; DigiKey 490-9146-1-ND
D1: 1N5819; D_DO-41_SOD81_P10.16mm_Horizontal; MPN 1N5819RLG; DigiKey 1N5819RLGOSCT-ND
FB1, FB2: Ferrite bead; R_Axial_DIN0309_L9.0mm_D3.2mm_P12.70mm_Horizontal; MPN 2743002112; DigiKey 1934-1477-1-ND
H1, H2: MountingHole_3.2mm_M3_Pad
J1: IRQDMA_JP; PinHeader_2x09_P2.54mm_Vertical; MPN 77313-118-18LF; DigiKey 609-77313-118-18LF-ND
J3: Bus_ISA_8bit; BUS_PC_chamfer
J5: SJ1-3535NG; Jack_3.5mm_CUI_SJ1-3535NG_Horizontal; MPN SJ1-3535NG; DigiKey CP1-3535NG-ND
J6: UART_TX; PinHeader_1x02_P2.54mm_Vertical; MPN 77311-118-02LF; DigiKey 609-4434-ND
J7: USB power jumper; PinHeader_1x02_P2.54mm_Vertical; MPN 77311-118-02LF; DigiKey 609-4434-ND
R1: 1K; R_Axial_DIN0207_L6.3mm_D2.5mm_P10.16mm_Horizontal; MPN MFR-25FBF52-1K; DigiKey 1.00KXBK-ND
R2, R5, R6: 15K; R_Axial_DIN0207_L6.3mm_D2.5mm_P10.16mm_Horizontal; MPN MFR-25FBF52-15K; DigiKey 15.0KXBK-ND
R3, R4: 220; R_Axial_DIN0207_L6.3mm_D2.5mm_P10.16mm_Horizontal; MPN RNMF14FTC220R; DigiKey S220CACT-ND
R17: 10K; R_Axial_DIN0207_L6.3mm_D2.5mm_P10.16mm_Horizontal; MPN MFR-25FBF52-10K; DigiKey 10.0KXBK-ND
R18: 100K; R_Axial_DIN0207_L6.3mm_D2.5mm_P10.16mm_Horizontal; MPN MFR-25FBF52-100K; DigiKey 100KXBK-ND
U1: Pico; RPi_Pico_SMD_TH_USB_NoSWD; MPN SC0915; DigiKey 2648-SC0915CT-ND
U2: 74AHC244; DIP-20_W7.62mm; MPN SN74AHC244N; DigiKey 296-4585-5-ND
U3, U4: SN74CB3T3257; TSSOP-16_4.4x5mm_P0.65mm_HandSolder_TestPads; MPN SN74CB3T3257PWR; DigiKey 296-17850-1-ND
U5: 74AHC14; DIP-14_W7.62mm; MPN SN74AHC14N; DigiKey 296-4550-5-ND
U6, U7: 74AHC00; DIP-14_W7.62mm; MPN SN74AHC00N; DigiKey 296-4510-5-ND
U8: APS6404L-3SQR-SN; SOIC-8_3.9x4.9mm_P1.27mm; MPN APS6404L-3SQR-SN; DigiKey 1528-4677-ND (Adafruit 4677 (64Mbit QSP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
U10: 74AHCT126; DIP-14_W7.62mm; MPN SN74AHCT126N; DigiKey 296-4659-5-ND

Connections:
+3V3: C1.1, C3.1, C4.1, C5.1, C6.1, C7.1, C8.1, C9.1, C10.1, R1.1, R2.1, R17.1, U1.36 (3V3), U2.20 (VCC), U3.16 (VCC), U4.16 (VCC), U5.14 (VCC), U6.14 (VCC), U7.14 (VCC), U8.8 (VCC); also elsewhere on the board
+5V: C2.1, D1.2 (A), J3.3 (VCC), J3.29 (VCC), R4.2, R6.1; also elsewhere on the board
+12V: J3.9 (+12V); also elsewhere on the board
-12V: J3.7 (-12V); also elsewhere on the board
/VSYS: D1.1 (K), J7.1, U1.39 (VSYS)
A0: J3.62 (BA00), U3.2 (1B1)
A1: J3.61 (BA01), U3.5 (2B1)
A2: J3.60 (BA02), U3.14 (4B1)
A3: J3.59 (BA03), U3.11 (3B1)
A4: J3.58 (BA04), U4.2 (1B1)
A5: J3.57 (BA05), U4.5 (2B1)
A6: J3.56 (BA06), U4.14 (4B1)
A7: J3.55 (BA07), U4.11 (3B1)
A8: J3.54 (BA08), U2.6 (1A2)
A9: J3.53 (BA09), U2.8 (1A3)
AD0: U1.9 (GPIO6), U3.4 (1A)
AD1: U1.10 (GPIO7), U3.7 (2A)
AD2: U1.11 (GPIO8), U3.12 (4A)
AD3: U1.12 (GPIO9), U3.9 (3A)
AD4: U1.14 (GPIO10), U4.4 (1A)
AD5: U1.15 (GPIO11), U4.7 (2A)
AD6: U1.16 (GPIO12), U4.12 (4A)
AD7: U1.17 (GPIO13), U4.9 (3A)
ADS: U1.32 (GPIO27_ADC1), U3.1 (S), U4.1 (S), U5.13
AEN: J3.42 (AEN), U7.1
BCK: U1.22 (GPIO17); also elsewhere on the board
D0: J3.40 (DB0), U3.3 (1B2)
D1: J3.39 (DB1), U3.6 (2B2)
D2: J3.38 (DB2), U3.13 (4B2)
D3: J3.37 (DB3), U3.10 (3B2)
D4: J3.36 (DB4), U4.3 (1B2)
D5: J3.35 (DB5), U4.6 (2B2)
D6: J3.34 (DB6), U4.13 (4B2)
D7: J3.33 (DB7), U4.10 (3B2)
DACK: J1.14, J1.18, R6.2, U5.11, U7.2
DACK1: J1.13, J3.17 (~DACK1)
DACK3: J1.17, J3.15 (~DACK3)
DIN: U1.21 (GPIO16); also elsewhere on the board
DRQ: J1.12, J1.16, U2.3 (2Y0)
DRQ1: J1.11, J3.18 (DRQ1)
DRQ3: J1.15, J3.16 (DRQ3)
GND: C1.2, C2.2, C3.2, C4.2, C5.2, C6.2, C7.2, C8.2, C9.2, C10.2, C11.2, H1.1, H2.1, J3.1 (GND), J3.10 (GND), J3.31 (GND), J5.S, J6.2, R5.2, R18.2, U1.3 (GND), U1.8 (GND), U1.13 (GND), U1.18 (GND), U1.23 (GND), U1.28 (GND), U1.33 (AGND), U1.38 (GND), U1.42 (GND), U1.TP1, U2.4 (1A1), U2.10 (GND), U2.11 (2A3), U2.13 (2A2), U3.8 (GND), U4.8 (GND), U5.7 (GND), U6.7 (GND), U7.7 (GND), U8.3 (SIO2), U8.4 (VSS), U8.7 (SIO3), U10.2, U10.5; also elsewhere on the board
IRQ: J1.2, J1.4, J1.6, J1.8, J1.10, U2.5 (2Y1)
IRQ2: J1.1, J3.4 (IRQ2)
IRQ3: J1.3, J3.25 (IRQ3)
IRQ4: J1.5, J3.24 (IRQ4)
IRQ5: J1.7, J3.23 (IRQ5)
IRQ7: J1.9, J3.21 (IRQ7)
I/OCHRDY: J3.41 (IO_READY), U10.3
LRCK: U1.24 (GPIO18); also elsewhere on the board
unnamed: FB1.1, R3.2
unnamed: FB1.2, J5.T
unnamed: FB2.1, R4.1
unnamed: FB2.2, J5.R
unnamed: J7.2, U1.40 (VBUS)
unnamed: R3.1, U10.6
unnamed: U5.4, U6.9
unnamed: U5.6, U6.5
unnamed: U5.12, U6.1
unnamed: U6.4, U6.10, U7.3
unnamed: U6.3, U6.12
RA8: U1.19 (GPIO14), U2.14 (1Y2)
RA9: U1.20 (GPIO15), U2.12 (1Y3)
RDRQ: U1.29 (GPIO22), U2.17 (2A0)
RESET: J3.2 (RESET), R5.1, U5.9; also elsewhere on the board
RIRQ: U1.27 (GPIO21), U2.15 (2A1)
RTC: U1.26 (GPIO20), U2.18 (1Y0)
RUN: C11.1, R1.2, U1.30 (RUN), U5.8, U6.13
SPI_RX: U1.1 (GPIO0), U8.2 (SO/SIO)
SPI_SCK: U1.4 (GPIO2), U8.6 (SCLK)
SPI_TX: U1.5 (GPIO3), U8.5 (SI/SIO)
TC: J3.27 (TC), U2.2 (1A0)
UART_TX: J6.1, R17.2, U1.34 (GPIO28_ADC2), U5.1
USB_DM: U1.TP2; also elsewhere on the board
USB_DP: U1.TP3; also elsewhere on the board
~BUSOE: R2.2, U2.1 (1OE), U2.19 (2OE), U3.15 (~OE), U4.15 (~OE), U6.2, U6.11
~IOR: J3.14 (~IOR), U5.3
~IOW: J3.13 (~IOW), U5.5
~MIDI_DRV: U5.2, U10.4; also elsewhere on the board
~RDACK: U1.25 (GPIO19), U5.10
~RIOR: U1.7 (GPIO5), U6.8
~RIOW: U1.6 (GPIO4), U6.6
~RI/OCHRDY: R18.1, U1.31 (GPIO26_ADC0), U10.1
~SPI_CS: U1.2 (GPIO1), U8.1 (~CE)

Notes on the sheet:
Saves PIO instructions due to JMP limitations
DECOUPLING CAPS
I2S DAC
Disables ~{IOR} and ~{IOW} signals when other DMA in system happens
Latches ~{BUSOE} low after ADS is toggled for the first time, sets high on RESET
MIDI/DEBUG OUT
MOUNTING
MISC LEVEL SHIFT/BUFFER
IRQ/DMA SETTING
DACK INVERT
ADDR/DATA MUX/DEMUX
SAMPLE RAM
AEN IO MASKING
ISA AND RASPBERRY PI PICO
RESET CIRCUIT
I/OCHRDY OPEN DRAIN
74xx LOGIC PWR
U10 = 74AHCT126 @ +5V (TTL inputs take 3V3 logic) Pseudo open-drain: A=GND, OE=1 -> low, OE=0 -> Hi-Z Gates C/D + power unit: "Wavetable & line out" sheet
THT board v1.3.2: the GY-PCM5102 module option (v1.2 I2S_DAC1/J4, v1.3.0/v1.3.1 J10) is gone: U9 (TSSOP-20, on the card) is the DAC.
THT board: J2 (ISA debug header, never fitted) is removed - its pads blocked the ISA routing.

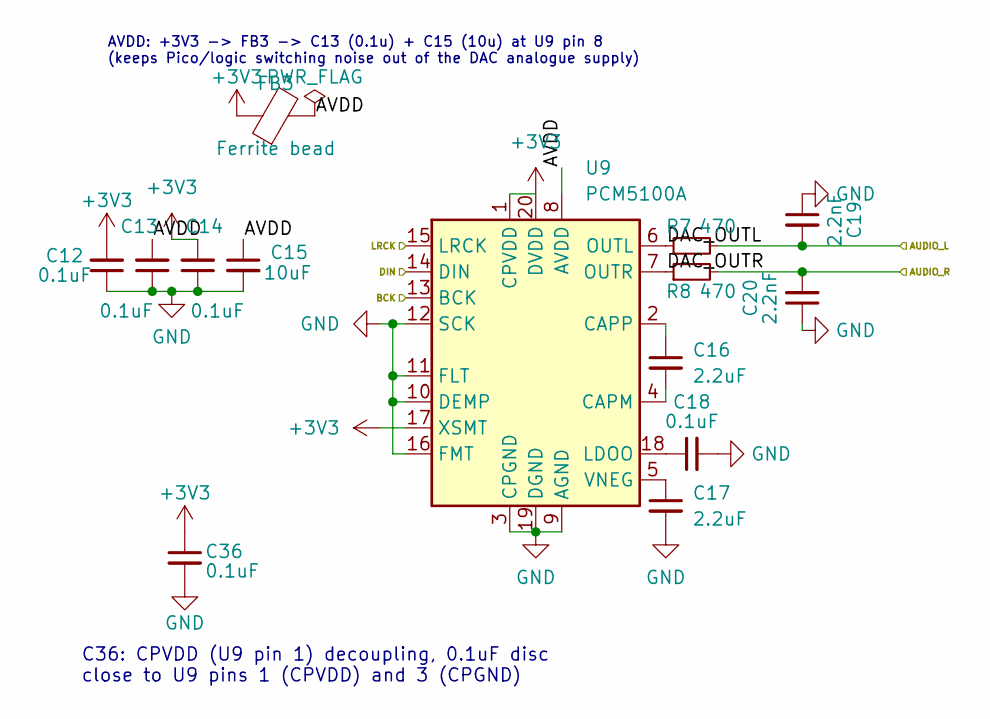
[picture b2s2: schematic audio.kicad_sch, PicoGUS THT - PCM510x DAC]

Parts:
C12, C13, C14, C18, C36: 0.1uF; C_Disc_D5.0mm_W2.5mm_P5.00mm; MPN RDER71H104K0M1H03A; DigiKey 490-9144-1-ND
C15: 10uF; C_Disc_D5.0mm_W2.5mm_P5.00mm; MPN RCER71H106MWK1H03B; DigiKey 490-11888-ND
C16, C17: 2.2uF; C_Disc_D5.0mm_W2.5mm_P5.00mm; MPN FG24X7R1H225KRT06; DigiKey 445-173378-1-ND
C19, C20: 2.2nF; C_Disc_D5.0mm_W2.5mm_P5.00mm; MPN FG28C0G1H222JNT06; DigiKey 445-173487-1-ND
FB3: Ferrite bead; R_Axial_DIN0309_L9.0mm_D3.2mm_P12.70mm_Horizontal; MPN 2743002112; DigiKey 1934-1477-1-ND
R7, R8: 470; R_Axial_DIN0207_L6.3mm_D2.5mm_P10.16mm_Horizontal; MPN RNMF14FTC470R; DigiKey S470CACT-ND
U9: PCM5100A; TSSOP-20_4.4x6.5mm_P0.65mm_HandSolder_TestPads; MPN PCM5100APWR; DigiKey 296-36705-1-ND

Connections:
+3V3: C12.2, C14.2, C36.1, FB3.1, U9.1 (CPVDD), U9.17 (XSMT), U9.20 (DVDD); also elsewhere on the board
/PCM5100 audio/AUDIO_L: C19.2, R7.2; also elsewhere on the board
/PCM5100 audio/AUDIO_R: C20.2, R8.2; also elsewhere on the board
/PCM5100 audio/AVDD: C13.2, C15.1, FB3.2, U9.8 (AVDD)
/PCM5100 audio/DAC_OUTL: R7.1, U9.6 (OUTL)
/PCM5100 audio/DAC_OUTR: R8.1, U9.7 (OUTR)
BCK: U9.13 (BCK); also elsewhere on the board
DIN: U9.14 (DIN); also elsewhere on the board
GND: C12.1, C13.1, C14.1, C15.2, C17.2, C18.2, C19.1, C20.1, C36.2, U9.3 (CPGND), U9.9 (AGND), U9.10 (DEMP), U9.11 (FLT), U9.12 (SCK), U9.16 (FMT), U9.19 (DGND); also elsewhere on the board
LRCK: U9.15 (LRCK); also elsewhere on the board
unnamed: C16.2, U9.4 (CAPM)
unnamed: C16.1, U9.2 (CAPP)
unnamed: C18.1, U9.18 (LDOO)
unnamed: C17.1, U9.5 (VNEG)

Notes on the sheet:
AVDD: +3V3 -> FB3 -> C13 (0.1u) + C15 (10u) at U9 pin 8 (keeps Pico/logic switching noise out of the DAC analogue supply)
C36: CPVDD (U9 pin 1) decoupling, 0.1uF disc close to U9 pins 1 (CPVDD) and 3 (CPGND)
